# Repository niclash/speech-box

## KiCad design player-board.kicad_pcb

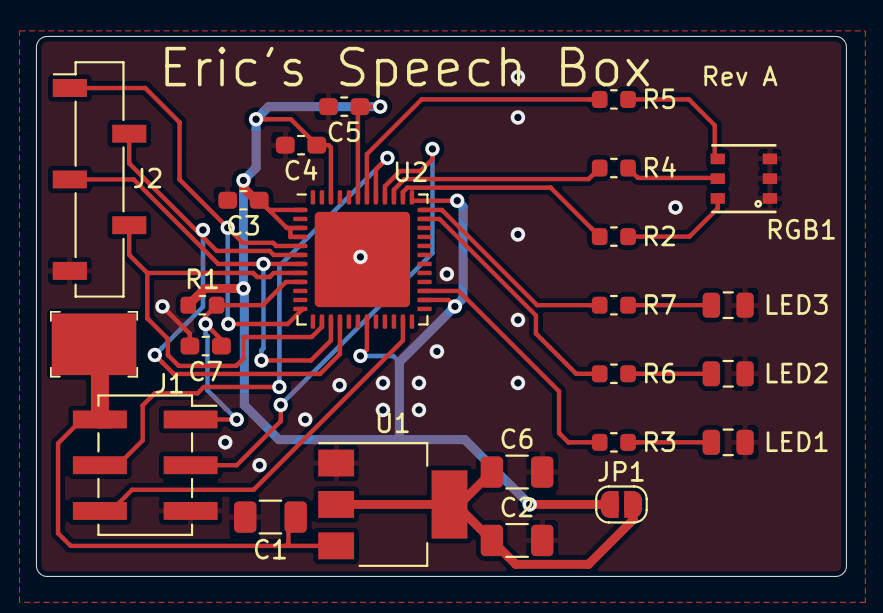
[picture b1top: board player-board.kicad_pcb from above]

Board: 2 copper layers, 45.0 x 30.0 mm, 23 parts (0 on the bottom side), 24 nets.

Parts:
C1, C2, C6: 10uF; C_1206_3216Metric
C3, C4, C5: 1uF; C_0603_1608Metric_Pad1.05x0.95mm_HandSolder
C7: 0.1uF; C_0603_1608Metric_Pad1.05x0.95mm_HandSolder
J1: Conn_02x03_Odd_Even; PinSocket_2x03_P2.54mm_Vertical_SMD
J2: Conn_01x05; PinSocket_1x05_P2.54mm_Vertical_SMD_Pin1Left
JP1: Jumper_2_Bridged; SolderJumper-2_P1.3mm_Open_RoundedPad1.0x1.5mm
LED1, LED2, LED3: Green; R_0805_2012Metric
R1: 10k; R_0603_1608Metric
R2, R3, R4, R5, R6, R7: 1k; R_0603_1608Metric
RGB1: LED_RGB; FM-Z3535RGBA
U1: AMS1117; SOT-223-3_TabPin2
U2: ESP32-PICO-D4; QFN-48-1EP_7x7mm_P0.5mm_EP5.3x5.3mm

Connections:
+3V3: C3.1, C4.1, C5.1, JP1.1, R1.1, U2.1, U2.3, U2.4, U2.19, U2.26, U2.37, U2.43, U2.46
+5V: C1.1, J1.2, U1.3
EN: C7.1, J1.1, R1.2, U2.9
GND: C1.2, C2.2, C3.2, C4.2, C5.2, C6.2, C7.2, J1.5, J2.5, LED1.1, LED2.1, LED3.1, RGB1.1, RGB1.2, RGB1.3, U1.1, U2.49
unnamed: C2.1, C6.1, JP1.2, U1.2
unnamed: J2.1, U2.5, U2.12
unnamed: J2.2, U2.6, U2.16
unnamed: J2.3, U2.7, U2.15
unnamed: J2.4, U2.8, U2.14
unnamed: LED1.2, R3.2
unnamed: LED2.2, R6.2
unnamed: LED3.2, R7.2
unnamed: R2.1, U2.38
unnamed: R2.2, RGB1.6
unnamed: R3.1, U2.27
unnamed: R4.1, U2.39
unnamed: R4.2, RGB1.5
unnamed: R5.1, U2.42
unnamed: R5.2, RGB1.4
unnamed: R6.1, U2.35
unnamed: R7.1, U2.36
PGM: J1.6, U2.23
RXD: J1.3, U2.40
TXD: J1.4, U2.41

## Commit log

2019-11-12 First trial
2019-11-12 Adding cap on EN.
2019-11-13 Forgot to commit file.
2019-11-13 Different footprint on ESP32-PICO
